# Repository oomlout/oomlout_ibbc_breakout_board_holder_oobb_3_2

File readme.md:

# IBBC Breakout Board Holder OOBB 3 x 2
A breakout board holder for ibbc interface boards.

## schematic  
  
[schematic (pdf)](kicad/current_version/working/working_schematic.pdf)  

## pcb  

[board (pdf)](kicad/current_version/working/working.pdf)  

## corel working

## working_bom
| Id | Designator | Footprint | Quantity | Designation | Supplier and ref |  | None | 
| --- | --- | --- | --- | --- | --- | --- | --- | 
| 1 | H2,H4,H3,H1 | [electronic_mounting_hole_m3](https://github.com/oomlout/oomlout_oomp_part_src/tree/main/parts/electronic_mounting_hole_m3/working) | 4 | mhm3 |  |  | [''] | 
| 2 | R1,R2 | [electronic_resistor_0603_4700_ohm](https://github.com/oomlout/oomlout_oomp_part_src/tree/main/parts/electronic_resistor_0603_4700_ohm/working) | 2 | r6o472 |  |  | [''] | 
| 3 | J3,J4 | [electronic_header_2d54_mm_6_pin](https://github.com/oomlout/oomlout_oomp_part_src/tree/main/parts/electronic_header_2d54_mm_6_pin/working) | 2 | hi16p |  |  | [''] | 
| 4 | J2,J1 | [electronic_header_1_mm_jst_sh_4_pin_surface_mount_right_angle](https://github.com/oomlout/oomlout_oomp_part_src/tree/main/parts/electronic_header_1_mm_jst_sh_4_pin_surface_mount_right_angle/working) | 2 | h4psmra |  |  | [''] | 
| 5 | U1 | [electronic_interposer_soic_14_wide_i2c_landing](https://github.com/oomlout/oomlout_oomp_part_src/tree/main/parts/electronic_interposer_soic_14_wide_i2c_landing/working) | 1 | insoic14wi2cland |  |  | [''] | 

## working_parts
| designator | oomp_key | placed | note | position_x | position_y | rotation | offset_x | offset_y | 
| --- | --- | --- | --- | --- | --- | --- | --- | --- | 
| H1 | [oomp_electronic_mounting_hole_m3](https://github.com/oomlout/oomlout_oomp_part_src/tree/main/parts/electronic_mounting_hole_m3/working) |  |  | -15 | -7.5 |  |  |  | 
| H2 | [oomp_electronic_mounting_hole_m3](https://github.com/oomlout/oomlout_oomp_part_src/tree/main/parts/electronic_mounting_hole_m3/working) |  |  | -15 | 7.5 |  |  |  | 
| H3 | [oomp_electronic_mounting_hole_m3](https://github.com/oomlout/oomlout_oomp_part_src/tree/main/parts/electronic_mounting_hole_m3/working) |  |  | 15 | -7.5 |  |  |  | 
| H4 | [oomp_electronic_mounting_hole_m3](https://github.com/oomlout/oomlout_oomp_part_src/tree/main/parts/electronic_mounting_hole_m3/working) |  |  | 15 | 7.5 |  |  |  | 
| J1 | [oomp_electronic_header_1_mm_jst_sh_4_pin_surface_mount_right_angle](https://github.com/oomlout/oomlout_oomp_part_src/tree/main/parts/electronic_header_1_mm_jst_sh_4_pin_surface_mount_right_angle/working) |  |  | 15 | 0 | 90 |  |  | 
| J2 | [oomp_electronic_header_1_mm_jst_sh_4_pin_surface_mount_right_angle](https://github.com/oomlout/oomlout_oomp_part_src/tree/main/parts/electronic_header_1_mm_jst_sh_4_pin_surface_mount_right_angle/working) |  |  | -15 | 0 | -90 |  |  | 
| U1 | [oomp_electronic_interposer_soic_14_wide_i2c_landing](https://github.com/oomlout/oomlout_oomp_part_src/tree/main/parts/electronic_interposer_soic_14_wide_i2c_landing/working) |  |  | -4 | -2 |  |  |  | 
| J3 | [oomp_electronic_header_2d54_mm_6_pin](https://github.com/oomlout/oomlout_oomp_part_src/tree/main/parts/electronic_header_2d54_mm_6_pin/working) |  |  | -6.35 | 10.16 | 90 |  |  | 
| J4 | [oomp_electronic_header_2d54_mm_6_pin](https://github.com/oomlout/oomlout_oomp_part_src/tree/main/parts/electronic_header_2d54_mm_6_pin/working) |  |  | 6.35 | -10.16 | -90 |  |  | 

## oomp_parts_summary
| index | designator | quantity | oomp_id | 
| --- | --- | --- | --- | 
| 1 | H2,H4,H3,H1 | 4 | [electronic_mounting_hole_m3](https://github.com/oomlout/oomlout_oomp_part_src/tree/main/parts/electronic_mounting_hole_m3/working)<br>[mhm3](https://github.com/oomlout/oomlout_oomp_part_src/tree/main/parts/electronic_mounting_hole_m3/working)<br>[Electronic Mounting Hole M3](https://github.com/oomlout/oomlout_oomp_part_src/tree/main/parts/electronic_mounting_hole_m3/working)<br><br> | 
| 2 | R1,R2 | 2 | [electronic_resistor_0603_4700_ohm](https://github.com/oomlout/oomlout_oomp_part_src/tree/main/parts/electronic_resistor_0603_4700_ohm/working)<br>[r6o472](https://github.com/oomlout/oomlout_oomp_part_src/tree/main/parts/electronic_resistor_0603_4700_ohm/working)<br>[Electronic Resistor 0603 4700 Ohm](https://github.com/oomlout/oomlout_oomp_part_src/tree/main/parts/electronic_resistor_0603_4700_ohm/working)<br>[LCSC - C25999<br>](https://lcsc.com/product-detail/C25999.html)[LCSC - C105428<br>](https://lcsc.com/product-detail/C105428.html)<br>[Uniroyal - 0603WAJ0472T5E]() [(L)  ](https://www.lcsc.com/search?q=0603WAJ0472T5E)[(D)  ](https://www.digikey.com/en/products?keywords=0603WAJ0472T5E)[(M)  ](https://www.mouser.com/Search/Refine?Keyword=0603WAJ0472T5E)[(N)  ](https://www.newark.com/search?st=0603WAJ0472T5E)[(SZ)  ](https://so.szlcsc.com/global.html?k=0603WAJ0472T5E)<br>[Uniroyal - 0603WAF4701T5E]() [(L)  ](https://www.lcsc.com/search?q=0603WAF4701T5E)[(D)  ](https://www.digikey.com/en/products?keywords=0603WAF4701T5E)[(M)  ](https://www.mouser.com/Search/Refine?Keyword=0603WAF4701T5E)[(N)  ](https://www.newark.com/search?st=0603WAF4701T5E)[(SZ)  ](https://so.szlcsc.com/global.html?k=0603WAF4701T5E)<br>[Yageo - RC0603JR-074K7L](https://www.yageo.com/en/Chart/Download/pdf/RC0603JR-074K7L) [(L)  ](https://www.lcsc.com/search?q=RC0603JR-074K7L)[(D)  ](https://www.digikey.com/en/products?keywords=RC0603JR-074K7L)[(M)  ](https://www.mouser.com/Search/Refine?Keyword=RC0603JR-074K7L)[(N)  ](https://www.newark.com/search?st=RC0603JR-074K7L)[(SZ)  ](https://so.szlcsc.com/global.html?k=RC0603JR-074K7L)<br> | 
| 3 | J3,J4 | 2 | [electronic_header_2d54_mm_6_pin](https://github.com/oomlout/oomlout_oomp_part_src/tree/main/parts/electronic_header_2d54_mm_6_pin/working)<br>[hi16p](https://github.com/oomlout/oomlout_oomp_part_src/tree/main/parts/electronic_header_2d54_mm_6_pin/working)<br>[Electronic Header 2D54 Mm 6 Pin](https://github.com/oomlout/oomlout_oomp_part_src/tree/main/parts/electronic_header_2d54_mm_6_pin/working)<br><br> | 
| 4 | J2,J1 | 2 | [electronic_header_1_mm_jst_sh_4_pin_surface_mount_right_angle](https://github.com/oomlout/oomlout_oomp_part_src/tree/main/parts/electronic_header_1_mm_jst_sh_4_pin_surface_mount_right_angle/working)<br>[h4psmra](https://github.com/oomlout/oomlout_oomp_part_src/tree/main/parts/electronic_header_1_mm_jst_sh_4_pin_surface_mount_right_angle/working)<br>[Electronic Header 1 Mm Jst Sh 4 Pin Surface Mount Right Angle](https://github.com/oomlout/oomlout_oomp_part_src/tree/main/parts/electronic_header_1_mm_jst_sh_4_pin_surface_mount_right_angle/working)<br>[LCSC - C145956<br>](https://lcsc.com/product-detail/C145956.html)[LCSC - C2906270<br>](https://lcsc.com/product-detail/C2906270.html)<br>[JST - SM04B-SRSS-TB](https://www.jst-mfg.com/product/index.php?series=231) [(L)  ](https://www.lcsc.com/search?q=SM04B-SRSS-TB)[(D)  ](https://www.digikey.com/en/products?keywords=SM04B-SRSS-TB)[(M)  ](https://www.mouser.com/Search/Refine?Keyword=SM04B-SRSS-TB)[(N)  ](https://www.newark.com/search?st=SM04B-SRSS-TB)[(SZ)  ](https://so.szlcsc.com/global.html?k=SM04B-SRSS-TB)<br> | 
| 5 | U1 | 1 | [electronic_interposer_soic_14_wide_i2c_landing](https://github.com/oomlout/oomlout_oomp_part_src/tree/main/parts/electronic_interposer_soic_14_wide_i2c_landing/working)<br>[insoic14wi2cland](https://github.com/oomlout/oomlout_oomp_part_src/tree/main/parts/electronic_interposer_soic_14_wide_i2c_landing/working)<br>[Electronic Interposer Soic 14 Wide I2C Landing](https://github.com/oomlout/oomlout_oomp_part_src/tree/main/parts/electronic_interposer_soic_14_wide_i2c_landing/working)<br><br> | 

Search Links: (L) - lcsc, (D) - digikey, (M) - mouser, (N) - newark, (SZ) - szlcsc

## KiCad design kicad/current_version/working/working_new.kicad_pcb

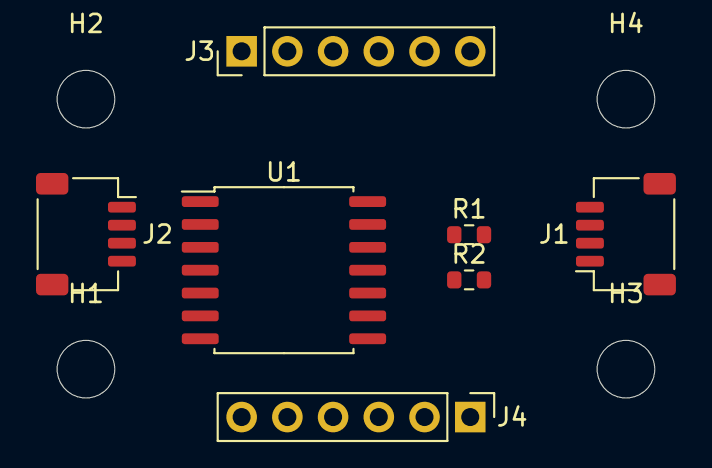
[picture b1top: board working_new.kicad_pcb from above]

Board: 2 copper layers, 11 parts (0 on the bottom side), 6 nets, no tracks yet.

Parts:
H1, H2, H3, H4: mhm3; mhm3_electronic_mounting_hole_m3
J1, J2: h4psmra; h4psmra_electronic_header_1_mm_jst_sh_4_pin_surface_mount_r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
J3, J4: hi16p; hi16p_electronic_header_2d54_mm_6_pin
R1, R2: r6o472; r6o472_electronic_resistor_0603_4700_ohm
U1: insoic14wi2cland; insoic14wi2cland_electronic_interposer_soic_14_wide_i2c_lan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

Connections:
+3V3: J1.2, J2.2, J3.2, R1.1, R2.1, U1.2 (___3v3)
/address: J3.6, U1.6 (___address)
/cs: J3.5, U1.5 (___cs)
/scl_3v3: J1.4, J2.4, J3.4, R2.2, U1.4 (___scl_3v3)
/sda_3v3: J1.3, J2.3, J3.3, R1.2, U1.3 (___sda_3v3)
GND: J1.1, J2.1, J3.1, U1.1 (___gnd)

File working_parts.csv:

designator,oomp_key,placed,note,position_x,position_y,rotation,offset_x,offset_y
H1,oomp_electronic_mounting_hole_m3,,,-15,-7.5,,,
H2,oomp_electronic_mounting_hole_m3,,,-15,7.5,,,
H3,oomp_electronic_mounting_hole_m3,,,15,-7.5,,,
H4,oomp_electronic_mounting_hole_m3,,,15,7.5,,,
J1,oomp_electronic_header_1_mm_jst_sh_4_pin_surface_mount_right_angle,,,15,0,90,,
J2,oomp_electronic_header_1_mm_jst_sh_4_pin_surface_mount_right_angle,,,-15,0,-90,,
U1,oomp_electronic_interposer_soic_14_wide_i2c_landing,,,-4,-2,,,
J3,oomp_electronic_header_2d54_mm_6_pin,,,-6.35,10.16,90,,
J4,oomp_electronic_header_2d54_mm_6_pin,,,6.35,-10.16,-90,,

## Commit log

2023-09-03 inintial working
2023-09-03 added generations
2023-09-03 added resolutions
2023-09-03 all generated
2023-09-03 commiting after auto generation
2023-09-03 update to images
2023-09-04 gitignore update
2023-09-04 ready to order boards
2023-09-04 updated generate
2023-09-04 production files
